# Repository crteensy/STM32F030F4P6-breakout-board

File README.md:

# STM32F030F4P6-breakout-board
STM32F030F4P6 breakout board pcb files and example code

Hackaday.io project: https://hackaday.io/project/4277-stm32f030f4p6-breakout-board  
(includes link to OSH Park for bare PCBs)

## Code::Blocks project
This repo includes a Code::Blocks project file which is pre-configured. However, it needs some adjustments to your own environment. These are the necessary steps:
* make sure then libopencm3 has been compiled as per their instructions
* correctly configure your compiler. The project looks for a compiler named "gcc-arm-none-eabi 4.9 2015q2". If you want to use a different one, change the project's top-level compiler to that.
* in the project's "Build Settings"->"Custom Variables": update the variable opencm3root to point at your libopencm3 root directory. Compiler and linker search paths use that variable.
* (optional) create a template: "File"->"Save Project as Template..."

The template (if you have created one; see the last step above) can then reused from within C::B's project wizard: "File"->"New"->"From Template" or "File"->"New"->"Project"->"User Templates"

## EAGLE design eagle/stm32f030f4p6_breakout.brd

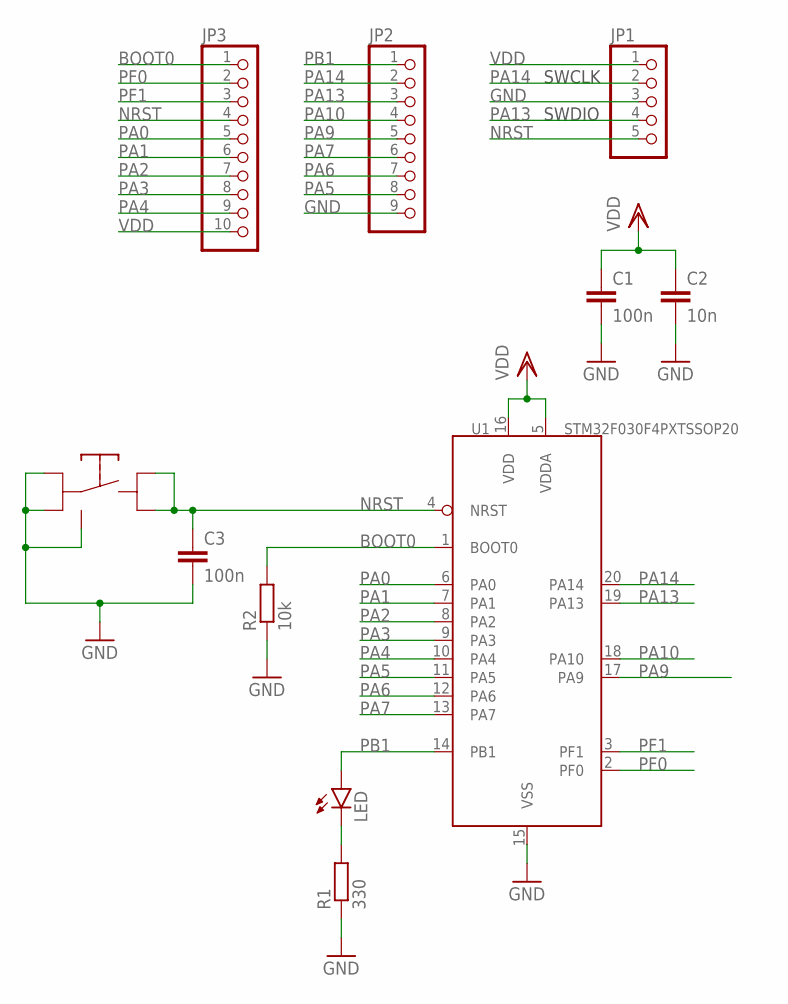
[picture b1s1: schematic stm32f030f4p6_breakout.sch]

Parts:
C1, C3: 100n; C0603
C2: 10n; C0603
JP1: PINHD-1X5/90; 1X05/90
JP2: PINHD-1X9; 1X09
JP3: PINHD-1X10; 1X10
LED: LED; LED-0603-CR
R1: 330; R0603
R2: 10k; R0603
RESET: KMR2XXG
U1: STM32F030F4PXTSSOP20; STM32F030F4PX_TSSOP20

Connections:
BOOT0: JP3.1, R2.2, U1.1 (BOOT0)
GND: C1.2, C2.2, C3.2, JP1.3, JP2.9, R1.1, R2.1, RESET.P$3 (3), RESET.P$4 (4), RESET.P$5 (G), U1.15 (VSS)
unnamed: LED.1 (C), R1.2
NRST: C3.1, JP1.5, JP3.4, RESET.P$1 (1), RESET.P$2 (2), U1.4 (NRST)
PA0: JP3.5, U1.6 (PA0)
PA1: JP3.6, U1.7 (PA1)
PA2: JP3.7, U1.8 (PA2)
PA3: JP3.8, U1.9 (PA3)
PA4: JP3.9, U1.10 (PA4)
PA5: JP2.8, U1.11 (PA5)
PA6: JP2.7, U1.12 (PA6)
PA7: JP2.6, U1.13 (PA7)
PA9: JP2.5, U1.17 (PA9)
PA10: JP2.4, U1.18 (PA10)
PA13: JP1.4, JP2.3, U1.19 (PA13)
PA14: JP1.2, JP2.2, U1.20 (PA14)
PB1: JP2.1, LED.2 (A), U1.14 (PB1)
PF0: JP3.2, U1.2 (PF0)
PF1: JP3.3, U1.3 (PF1)
VDD: C1.1, C2.1, JP1.1, JP3.10, U1.5 (VDDA), U1.16 (VDD)

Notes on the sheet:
SWDIO
SWCLK

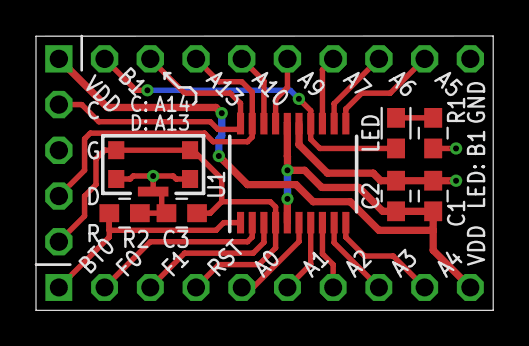
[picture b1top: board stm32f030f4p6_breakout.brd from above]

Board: 2 copper layers, 25.4 x 15.2 mm, 11 parts (1 on the bottom side), 20 nets.

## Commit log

2015-06-29 added files
2015-06-29 added project files
2015-06-29 updated project file
2015-06-29 updated elapsedMillis (initializer list)
2015-06-30 fixed indentation (tabs->spaces)
2015-07-13 added board files
2015-07-24 fixed build option: Release options are now appended to project options
2015-07-24 fixed build options: Release options are now appended to project options (+linker, +search directories)
2015-07-24 - added C std - removed systick namespace
2015-11-09 - added BOOT0 pulldown - silkscreen type slightly increased to 35mil - wider supply tracks - minor changes to routing
2015-12-02 added gerbers
